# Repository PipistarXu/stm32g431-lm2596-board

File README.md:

# STM32G431 + LM2596 Custom Board

## Project Status
- PCB design completed
- Assembly not started yet

## Goals
- Build a custom control/power board based on STM32G431.
- Use LM2596 buck stage for stable DC conversion.
- Complete bring-up with safe current-limited power-on.

## Confirmed Hardware Decisions
- MCU: **STM32G431** (UFQFPN48 package)
- Buck IC: **LM2596S-ADJ**
- Schottky diode: **1N5822**
  - Polarity rule: **K (stripe) -> SW**, **A -> GND**
- Inductor: **CDRH127/LDNP-330MC**
  - 33uH, 12x12mm footprint, height ~8mm
- Small capacitors (SMD): 0603, X7R preferred
- R4 package: 0402 (1005 Metric), value TBD by final schematic intent

## Current Risks / Open Items
- [ ] Verify D2 pad net with multimeter (must be SW/GND as expected)
- [ ] Confirm 8mm inductor height clearance with enclosure/mechanics
- [ ] Confirm 220uF capacitor package availability (6.3x5.4 may be tight)
- [ ] Finalize R4 resistance value
- [ ] Prepare first power-on with current limit (0.1A~0.2A)

## Repository Layout
- `docs/`: notes, checklist, images
- `hardware/kicad/`: source schematic + PCB
- `hardware/fabrication/`: gerber, drill, BOM, pick-and-place
- `hardware/datasheets/`: key PDFs
- `firmware/`: future STM32 firmware

## First Bring-Up (Summary)
1. Visual inspection (orientation, bridges, polarity)
2. Resistance checks (VIN-GND, 5V-GND/3V3-GND)
3. Power from bench supply with 0.1A current limit
4. Verify LM2596 output and thermal behavior
5. Increase current limit gradually

## Notes
- UFQFPN48 is difficult for hand soldering; hot-air and flux are strongly recommended.
- Always trust actual net connectivity + multimeter over silkscreen when conflict exists.

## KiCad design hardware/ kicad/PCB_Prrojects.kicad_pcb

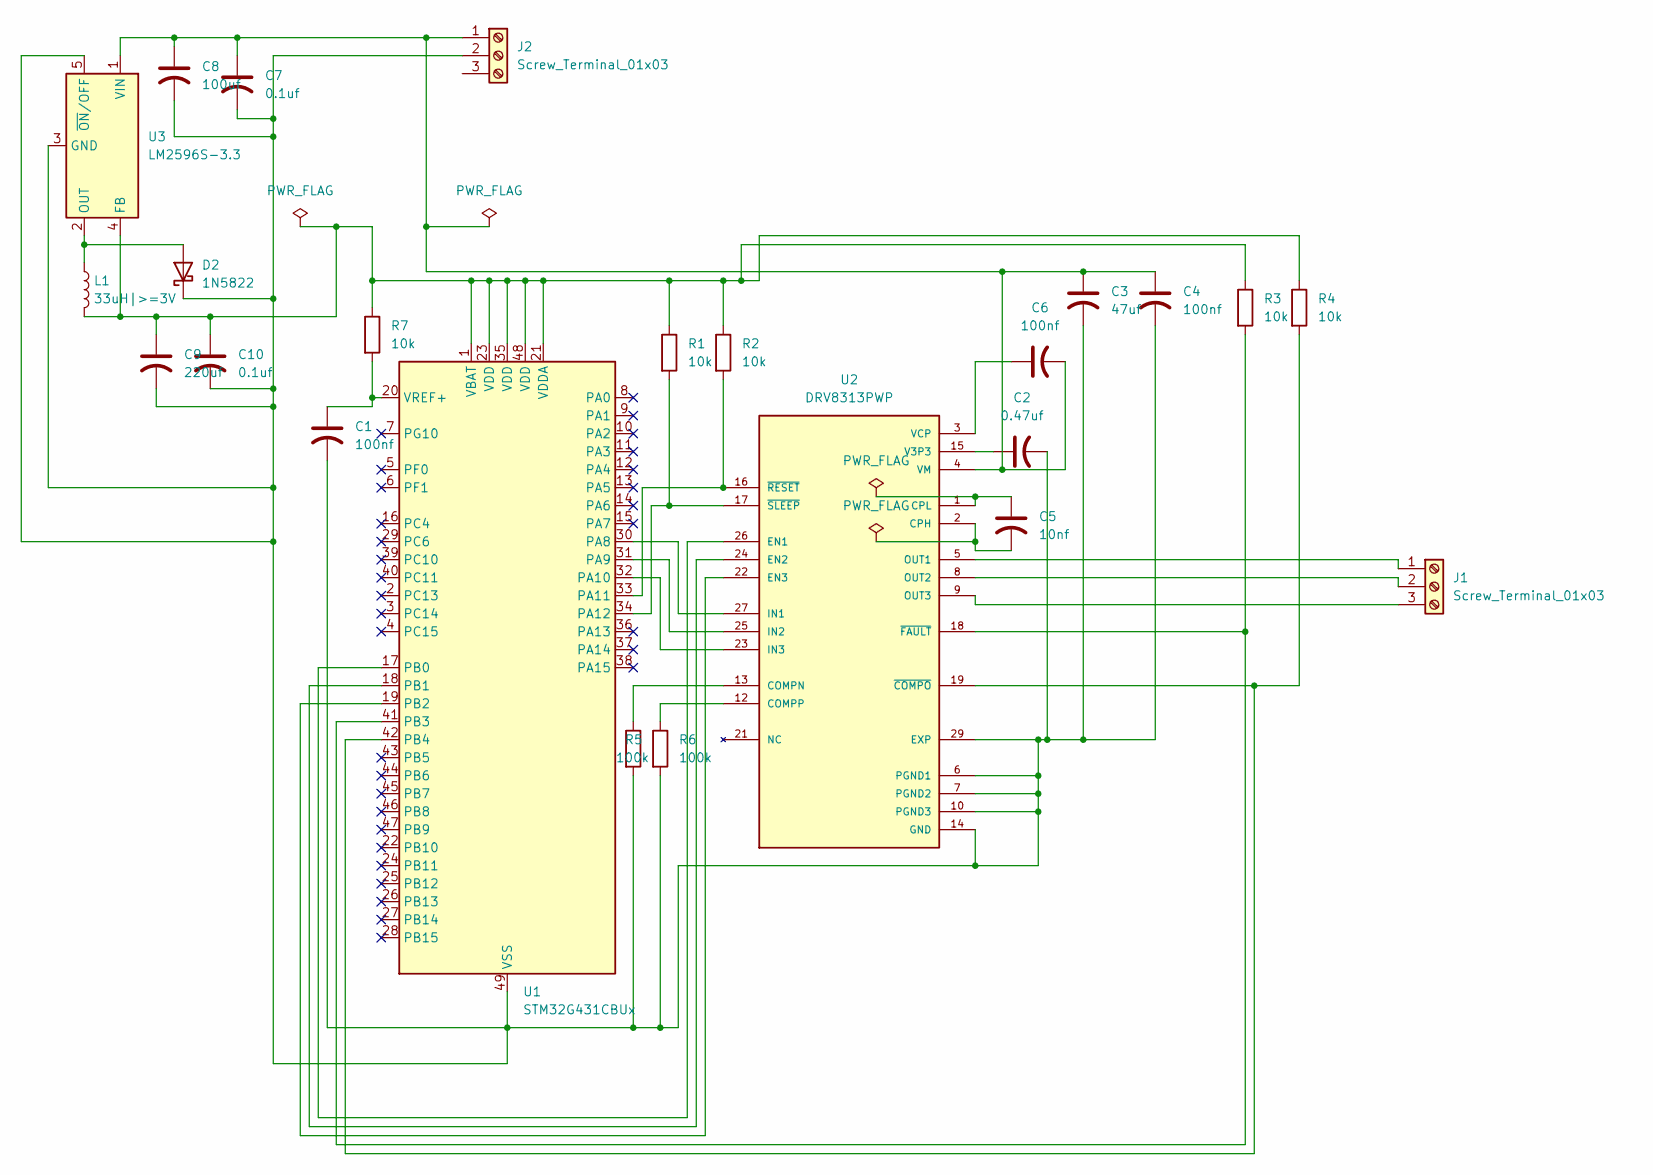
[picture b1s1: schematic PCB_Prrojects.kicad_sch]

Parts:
C1, C4, C6: 100nf; C_0603_1608Metric
C2: 0.47uf; C_0603_1608Metric
C3: 47uf; CP_Elec_6.3x5.4
C5: 10nf; C_0603_1608Metric
C7, C10: 0.1uf; C_0603_1608Metric
C8: 100uf; CP_Elec_6.3x5.4
C9: 220uf; CP_Elec_6.3x5.4
D2: 1N5822; D_DO-201AD_P15.24mm_Horizontal
J1, J2: Screw_Terminal_01x03; TerminalBlock_Xinya_XY308-2.54-3P_1x03_P2.54mm_Horizontal
L1: 33uH|>=3V; L_12x12mm_H6mm
R1, R2, R3, R4, R7: 10k; R_0603_1608Metric
R5, R6: 100k; R_0603_1608Metric
U1: STM32G431CBUx; QFN-48-1EP_7x7mm_P0.5mm_EP5.6x5.6mm
U2: DRV8313PWP; HTSSOP-28-1EP_4.4x9.7mm_P0.65mm_EP2.75x6.2mm; PARTREV D
U3: LM2596S-3.3; TO-263-5_TabPin3

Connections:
GND: C1.2, C2.2, C3.2, C4.2, C7.2, C8.2, C9.2, C10.2, D2.1 (K), J2.2, R5.2, R6.2, U1.49 (VSS), U2.6 (PGND1), U2.7 (PGND2), U2.10 (PGND3), U2.14 (GND), U2.20 (GND), U2.28 (GND), U2.29 (EXP), U3.3 (GND), U3.5 (~ON/OFF)
unnamed: D2.2 (A), L1.1, U3.2 (OUT)
unnamed: J1.1, U2.5 (OUT1)
unnamed: J1.2, U2.8 (OUT2)
unnamed: J1.3, U2.9 (OUT3)
unnamed: U1.30 (PA8), U2.27 (IN1)
unnamed: U1.31 (PA9), U2.25 (IN2)
unnamed: U1.32 (PA10), U2.23 (IN3)
unnamed: R2.2, U1.33 (PA11), U2.16 (~RESET)
unnamed: R1.2, U1.34 (PA12), U2.17 (~SLEEP)
unnamed: U1.17 (PB0), U2.26 (EN1)
unnamed: U1.18 (PB1), U2.24 (EN2)
unnamed: U1.19 (PB2), U2.22 (EN3)
unnamed: R3.2, U1.41 (PB3), U2.18 (~FAULT)
unnamed: R4.2, U1.42 (PB4), U2.19 (~COMPO)
unnamed: C9.1, C10.1, L1.2, R1.1, R2.1, R3.1, R4.1, R7.1, U1.1 (VBAT), U1.21 (VDDA), U1.23 (VDD), U1.35 (VDD), U1.48 (VDD), U3.4 (FB)
unnamed: C1.1, R7.2, U1.20 (VREF+)
unnamed: R5.1, U2.13 (COMPN)
unnamed: R6.1, U2.12 (COMPP)
unnamed: C5.2, U2.2 (CPH)
unnamed: C5.1, U2.1 (CPL)
unnamed: C2.1, U2.15 (V3P3)
unnamed: C6.1, U2.3 (VCP)
VM: C3.1, C4.1, C6.2, C7.1, C8.1, J2.1, U2.4 (VM), U2.11 (VM), U3.1 (VIN)

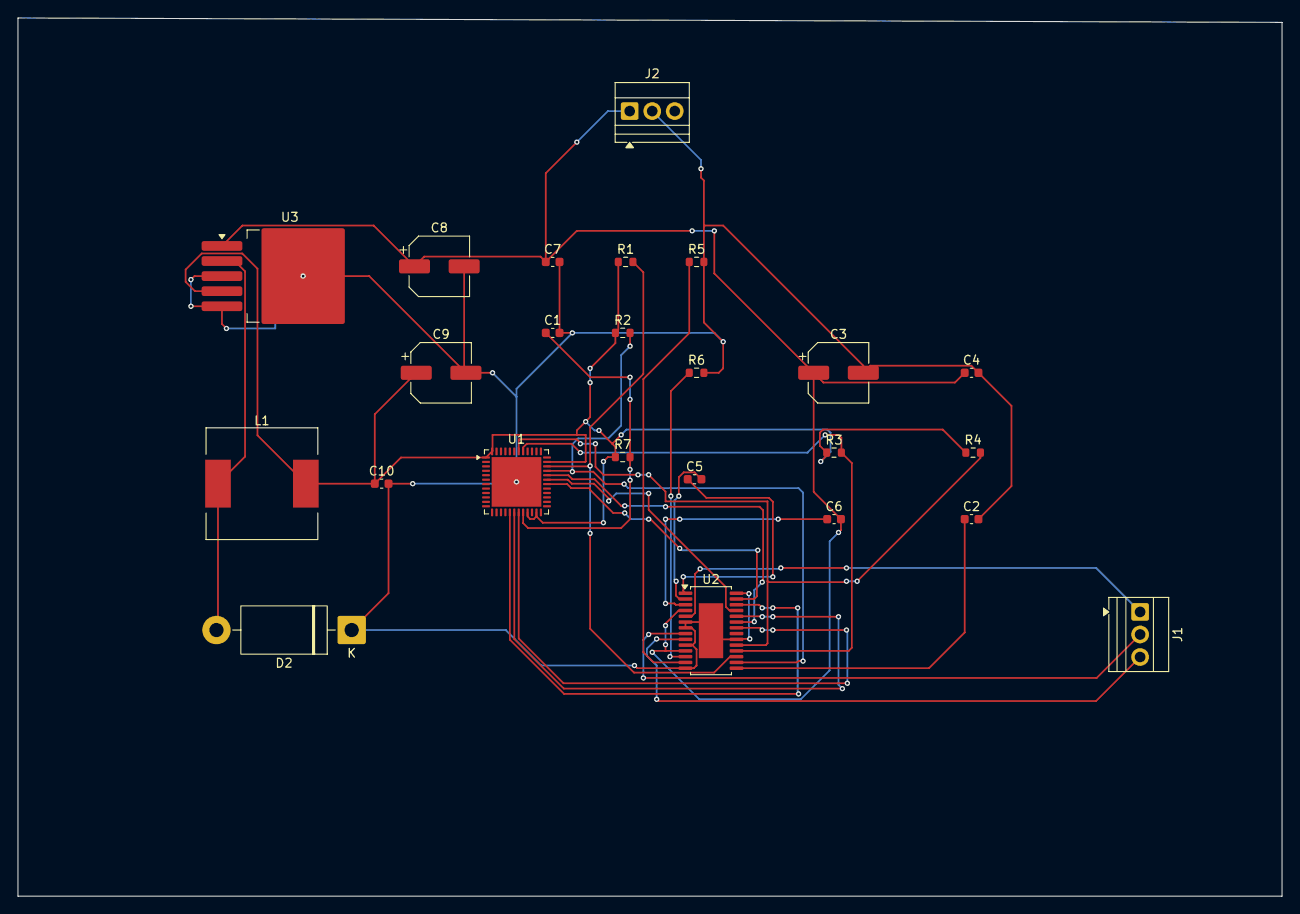
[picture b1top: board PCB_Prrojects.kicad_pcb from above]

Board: 2 copper layers, 142.5 x 99.0 mm, 24 parts (0 on the bottom side), 24 nets.

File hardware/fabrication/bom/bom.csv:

"Reference","Qty","Value","DNP","Exclude from BOM","Exclude from Board","Footprint","Datasheet","Check_prices","MANUFACTURER","MAXIMUM_PACKAGE_HEIGHT","MF","MP","Availability","Description","#"
"C1,C4,C6","3","100nf","","","","Capacitor_SMD:C_0603_1608Metric","","","","","","","","capacitor, US symbol","1"
"C2","1","0.47uf","","","","Capacitor_SMD:C_0603_1608Metric","","","","","","","","capacitor, US symbol","2"
"C3","1","47uf","","","","Capacitor_SMD:CP_Elec_6.3x5.4","","","","","","","","capacitor, US symbol","3"
"C5","1","10nf","","","","Capacitor_SMD:C_0603_1608Metric","","","","","","","","capacitor, US symbol","4"
"C7,C10","2","0.1uf","","","","Capacitor_SMD:C_0603_1608Metric","","","","","","","","capacitor, US symbol","5"
"C8","1","100uf","","","","Capacitor_SMD:CP_Elec_6.3x5.4","","","","","","","","capacitor, US symbol","6"
"C9","1","220uf","","","","Capacitor_SMD:CP_Elec_6.3x5.4","","","","","","","","capacitor, US symbol","7"
"D2","1","1N5822","","","","Diode_THT:D_DO-201AD_P15.24mm_Horizontal","http://www.vishay.com/docs/88526/1n5820.pdf","","","","","","","40V 3A Schottky Barrier Rectifier Diode, DO-201AD","8"
"J1,J2","2","Screw_Terminal_01x03","","","","TerminalBlock:TerminalBlock_Xinya_XY308-2.54-3P_1x03_P2.54mm_Horizontal","","","","","","","","Generic screw terminal, single row, 01x03, script generated (kicad-library-utils/schlib/autogen/connector/)","9"
"L1","1","33uH|>=3V","","","","Inductor_SMD:L_12x12mm_H6mm","","","","","","","","Inductor","10"
"R1,R2,R3,R4,R7","5","10k","","","","Resistor_SMD:R_0603_1608Metric","","","","","","","","Resistor","11"
"R5,R6","2","100k","","","","Resistor_SMD:R_0603_1608Metric","","","","","","","","Resistor","12"
"U1","1","STM32G431CBUx","","","","Package_DFN_QFN:QFN-48-1EP_7x7mm_P0.5mm_EP5.6x5.6mm","https://www.st.com/resource/en/datasheet/stm32g431cb.pdf","","","","","","","STMicroelectronics Arm Cortex-M4 MCU, 128KB flash, 32KB RAM, 170 MHz, 1.71-3.6V, 42 GPIO, UFQFPN48","13"
"U2","1","DRV8313PWP","","","","Package_SO:HTSSOP-28-1EP_4.4x9.7mm_P0.65mm_EP2.75x6.2mm","","https://www.snapeda.com/parts/DRV8313PWP/Texas+Instruments/v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","Texas Instruments","1.2 mm","Texas Instruments","DRV8313PWP","In Stock","65-V max 3-A peak 3-phase motor driver with integrated FETs","14"
"U3","1","LM2596S-3.3","","","","Package_TO_SOT_SMD:TO-263-5_TabPin3","http://www.ti.com/lit/ds/symlink/lm2596.pdf","","","","","","","3.3V 3A Step-Down Voltage Regulator, TO-263","15"
